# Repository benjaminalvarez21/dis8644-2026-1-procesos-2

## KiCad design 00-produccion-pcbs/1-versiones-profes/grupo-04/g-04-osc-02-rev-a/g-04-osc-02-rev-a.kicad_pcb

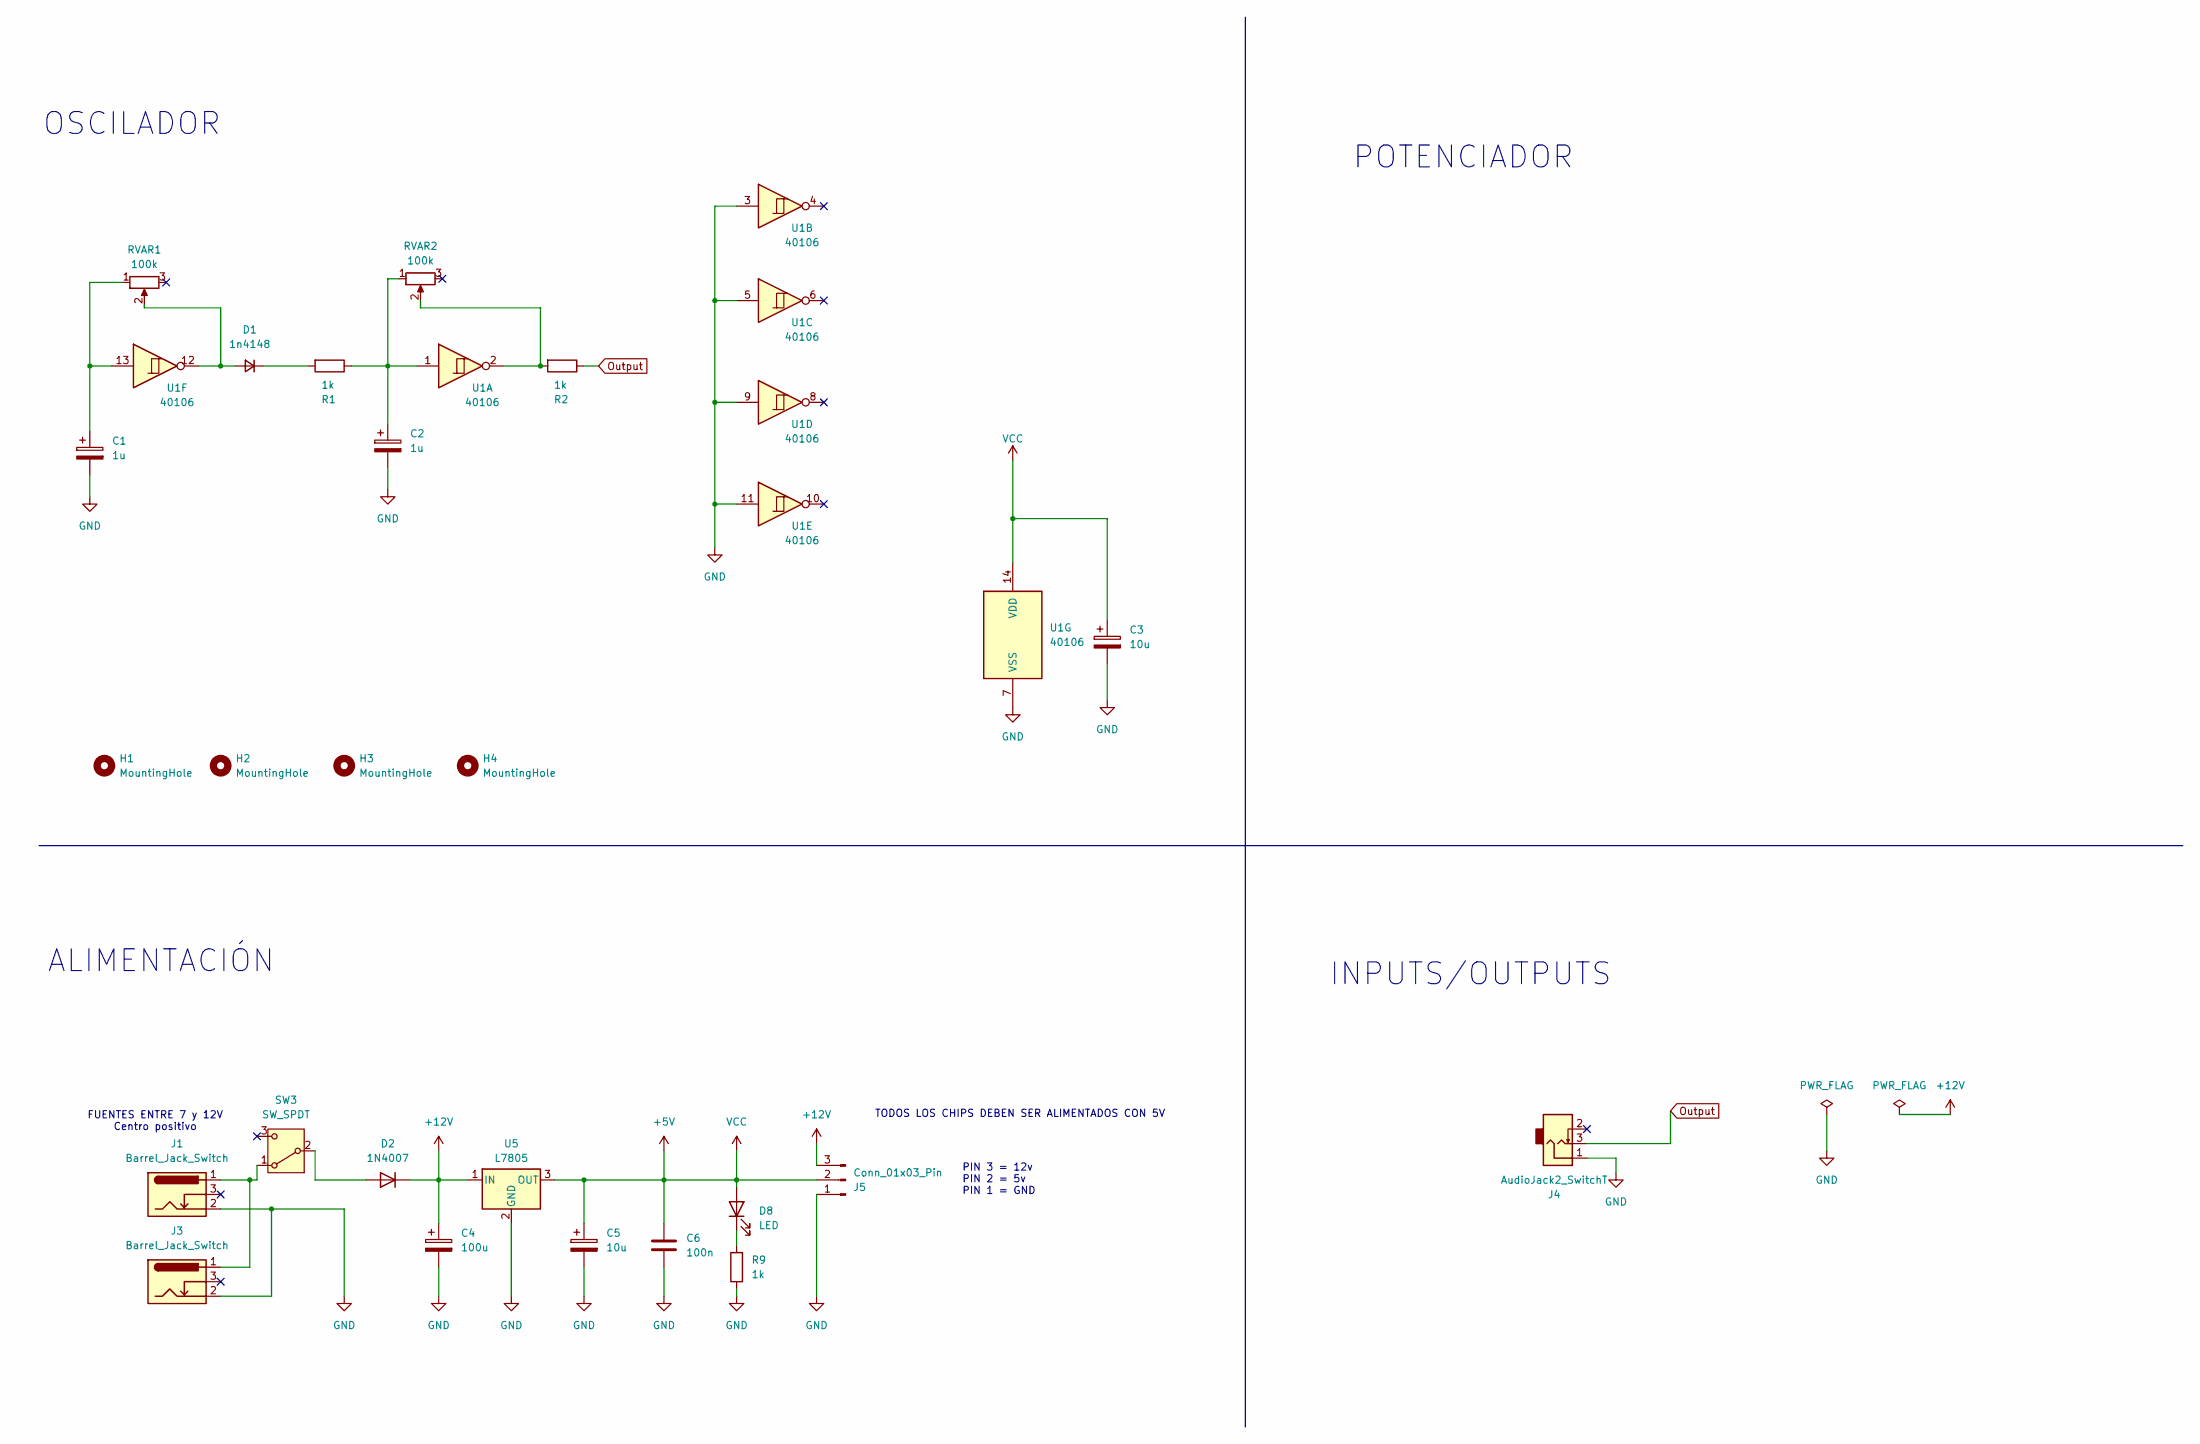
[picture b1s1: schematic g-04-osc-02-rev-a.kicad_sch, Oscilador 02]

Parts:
C1, C2: 1u; CP_Radial_D4.0mm_P2.00mm
C3, C5: 10u; CP_Radial_D4.0mm_P2.00mm
C4: 100u; CP_Radial_D8.0mm_P3.80mm
C6: 100n; C_Disc_D5.0mm_W2.5mm_P2.50mm
D1: 1n4148; D_DO-35_SOD27_P7.62mm_Horizontal
D2: 1N4007; D_DO-41_SOD81_P10.16mm_Horizontal
D8: LED; LED_D5.0mm
H1, H2, H3, H4: MountingHole; MountingHole_3.2mm_M3
J1, J3: Barrel_Jack_Switch; BarrelJack_Horizontal
J4: AudioJack2_SwitchT; PJ301M-12
J5: Conn_01x03_Pin; PinSocket_1x03_P2.54mm_Vertical
R1, R2, R9: 1k; R_Axial_DIN0207_L6.3mm_D2.5mm_P10.16mm_Horizontal
RVAR1, RVAR2: 100k; Potentiometer_Alps_RK163_Single_Horizontal
SW3: SW_SPDT; spdt_ssd12d00g3
U1: 40106; DIP-14_W7.62mm
U5: L7805; TO-220-3_Horizontal_TabDown

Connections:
+5V: C3.1, C5.1, C6.1, D8.2 (A), J5.2, U1.14 (VDD), U5.3 (OUT)
+12V: C4.1, D2.1 (K), J5.3, U5.1 (IN)
GND: C1.2, C2.2, C3.2, C4.2, C5.2, C6.2, J1.2, J3.2, J4.1, J5.1, R9.1, U1.3, U1.5, U1.7 (VSS), U1.9, U1.11, U5.2 (GND)
unnamed: C1.1, RVAR1.1, U1.13
unnamed: C2.1, R1.1, RVAR2.1, U1.1
unnamed: D1.2 (A), RVAR1.2, U1.12
unnamed: D1.1 (K), R1.2
unnamed: D2.2 (A), SW3.2 (B)
unnamed: D8.1 (K), R9.2
unnamed: R2.2, RVAR2.2, U1.2
unnamed: J1.1, J3.1, SW3.1 (A)
Output: J4.3, R2.1

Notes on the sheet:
POTENCIADOR
ALIMENTACIÓN
TODOS LOS CHIPS DEBEN SER ALIMENTADOS CON 5V
FUENTES ENTRE 7 y 12V Centro positivo
INPUTS/OUTPUTS
PIN 3 = 12v PIN 2 = 5v PIN 1 = GND
OSCILADOR

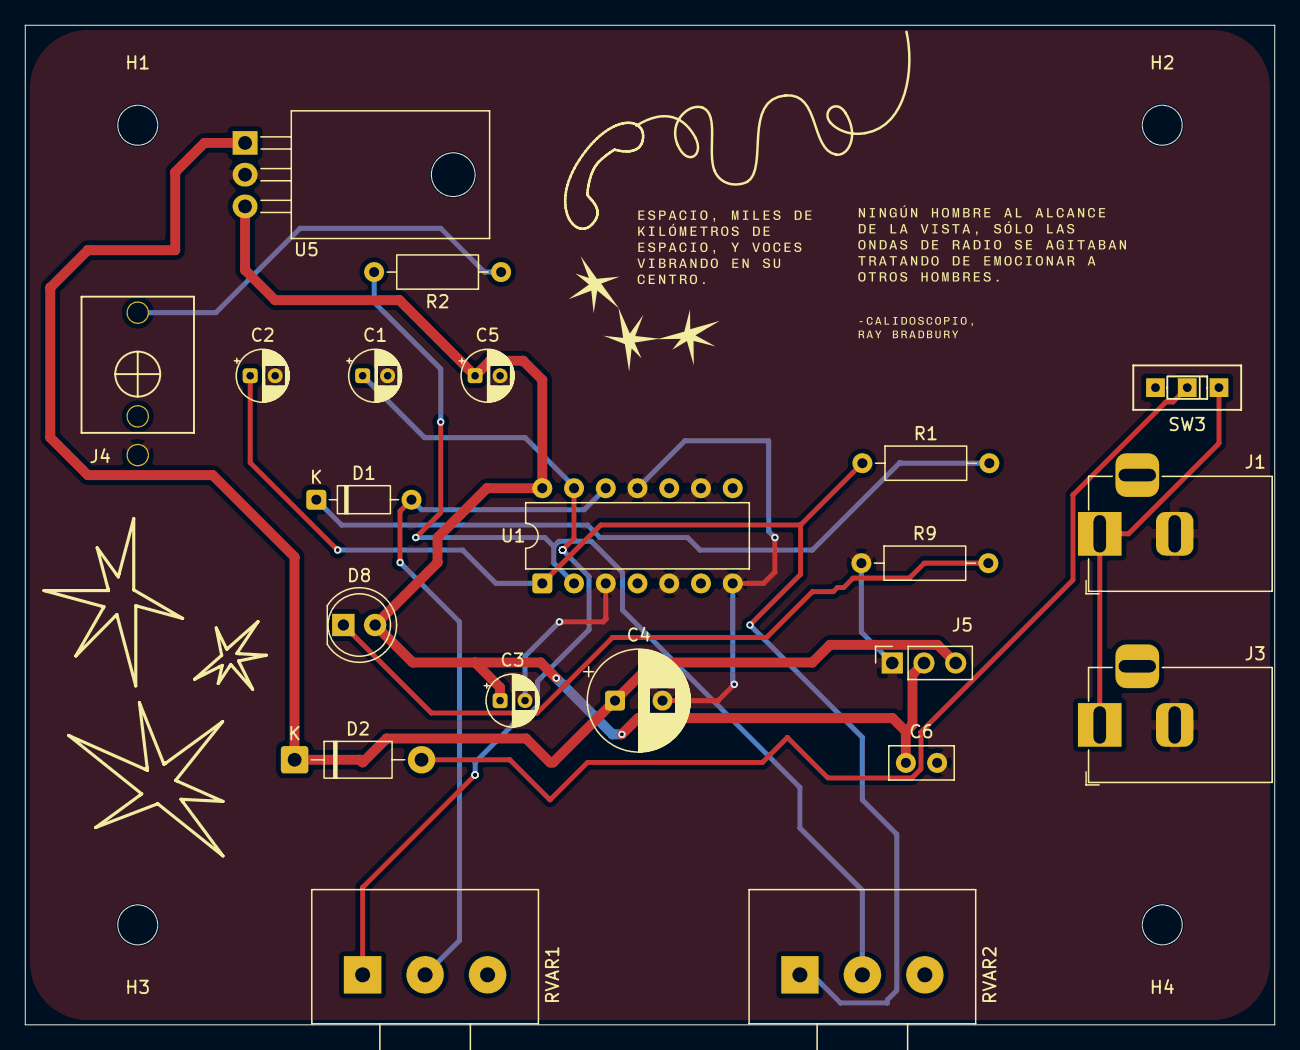
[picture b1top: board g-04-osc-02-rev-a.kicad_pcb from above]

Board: 2 copper layers, 100.0 x 80.0 mm, 25 parts (0 on the bottom side), 12 nets.

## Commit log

2026-05-15 corregidos
2026-05-17 Update README with mention of Bonvallet
    Added a note about Bonvallet and personal reflections.
2026-05-17 Add note about missing class due to health issues
2026-05-18 Update README with images and formatting adjustments
    Added images to README and removed extra whitespace.
2026-05-19 Add 'Feriado' section to README.md
2026-05-19 Add date to README for sesion-10a
2026-05-19 no-cambio-tamano-voy-denuevo
2026-05-19 Add date to README for sesion-11a
2026-05-22 Enhance README with KiCad usage instructions
    Added detailed instructions for using KiCad, including steps for schematic drawing, component association, and PCB design. Included a table for component names and footprints.
2026-05-22 Fix spelling and formatting in README.md
    Corrected spelling and formatting issues in README.
2026-05-22 sesion-in-correcta
2026-05-22 sesion-correcta
2026-05-23 sesion 10a
2026-05-24 Add date to sesion-10a README
2026-05-24 arreglo redacción
2026-05-25 banana
2026-05-25 gif01
2026-05-25 borrar archivo borrar
2026-05-25 seguir editando
2026-05-26 Add section on photography and technical images
    Added a new section discussing the differences between traditional and technical images, referencing Flusser's ideas.
2026-05-27 agregar
2026-05-28 imagenes
2026-05-29 avance de apuntes
2026-05-31 agrego ss
2026-06-01 Pequeñas faltas ortográficas XP
2026-06-01 falta agregar imagenes
2026-06-01 cambiar libreria por biblioteca
2026-06-02 correcion 10a
2026-06-02 Revise README with insights from recent sessions
    Updated README.md to reflect discussions from chapters 2, 3, 4, and 5, including insights on measurement, art, and photography.
2026-06-02 arreglo links
2026-06-03 cambiar-carpeta
2026-06-03 carpeta-correcta-espero
2026-06-03 Update README with YouTube links for protoboard
    Added YouTube links for protoboard functionality in documentation.
2026-06-03 agregar a
2026-06-03 agregar divs
2026-06-03 en edicion
2026-06-04 agregar index
2026-06-04 probar sch y pcb en mismo kicanvas
2026-06-05 Create oscilador2-01-v01
2026-06-05 Rename image.png to pcb-front-2.png
2026-06-05 ultimas-imagenes
2026-06-05 agrego apuntes
2026-06-05 Rename 21-ryukivol/sesion-12a/imagenes/20260529_124221 (1) (1).gif to 21-ryukivol/sesion-12a/circuito-01.gif
2026-06-05 agregar carpeta proyecto-03
2026-06-06 agregar grupo-04
2026-06-06 agregar grupo-06
2026-06-06 añadidoa g04-02
2026-06-07 imagenes-extra
2026-06-11 partitura-y-2-canciones
2026-06-12 agrego apuntes(? presentación
2026-06-12 Update README with weekly reading and materials list
    Added weekly reading and material list for project.
2026-06-16 martes 16 de junio, avance.md
2026-06-17 Add health-related note to README
2026-06-17 agrego bom grupo 02
2026-06-18 Change images in README from PNG to JPEG
    Updated image formats in README.md from PNG to JPEG.
2026-06-18 faltan imgenes
2026-06-19 avance-texto-falta-integracion
2026-06-23 Expand README with PCB and project details
    Added detailed instructions on PCB design and file export, along with creative project ideas for music and art.
